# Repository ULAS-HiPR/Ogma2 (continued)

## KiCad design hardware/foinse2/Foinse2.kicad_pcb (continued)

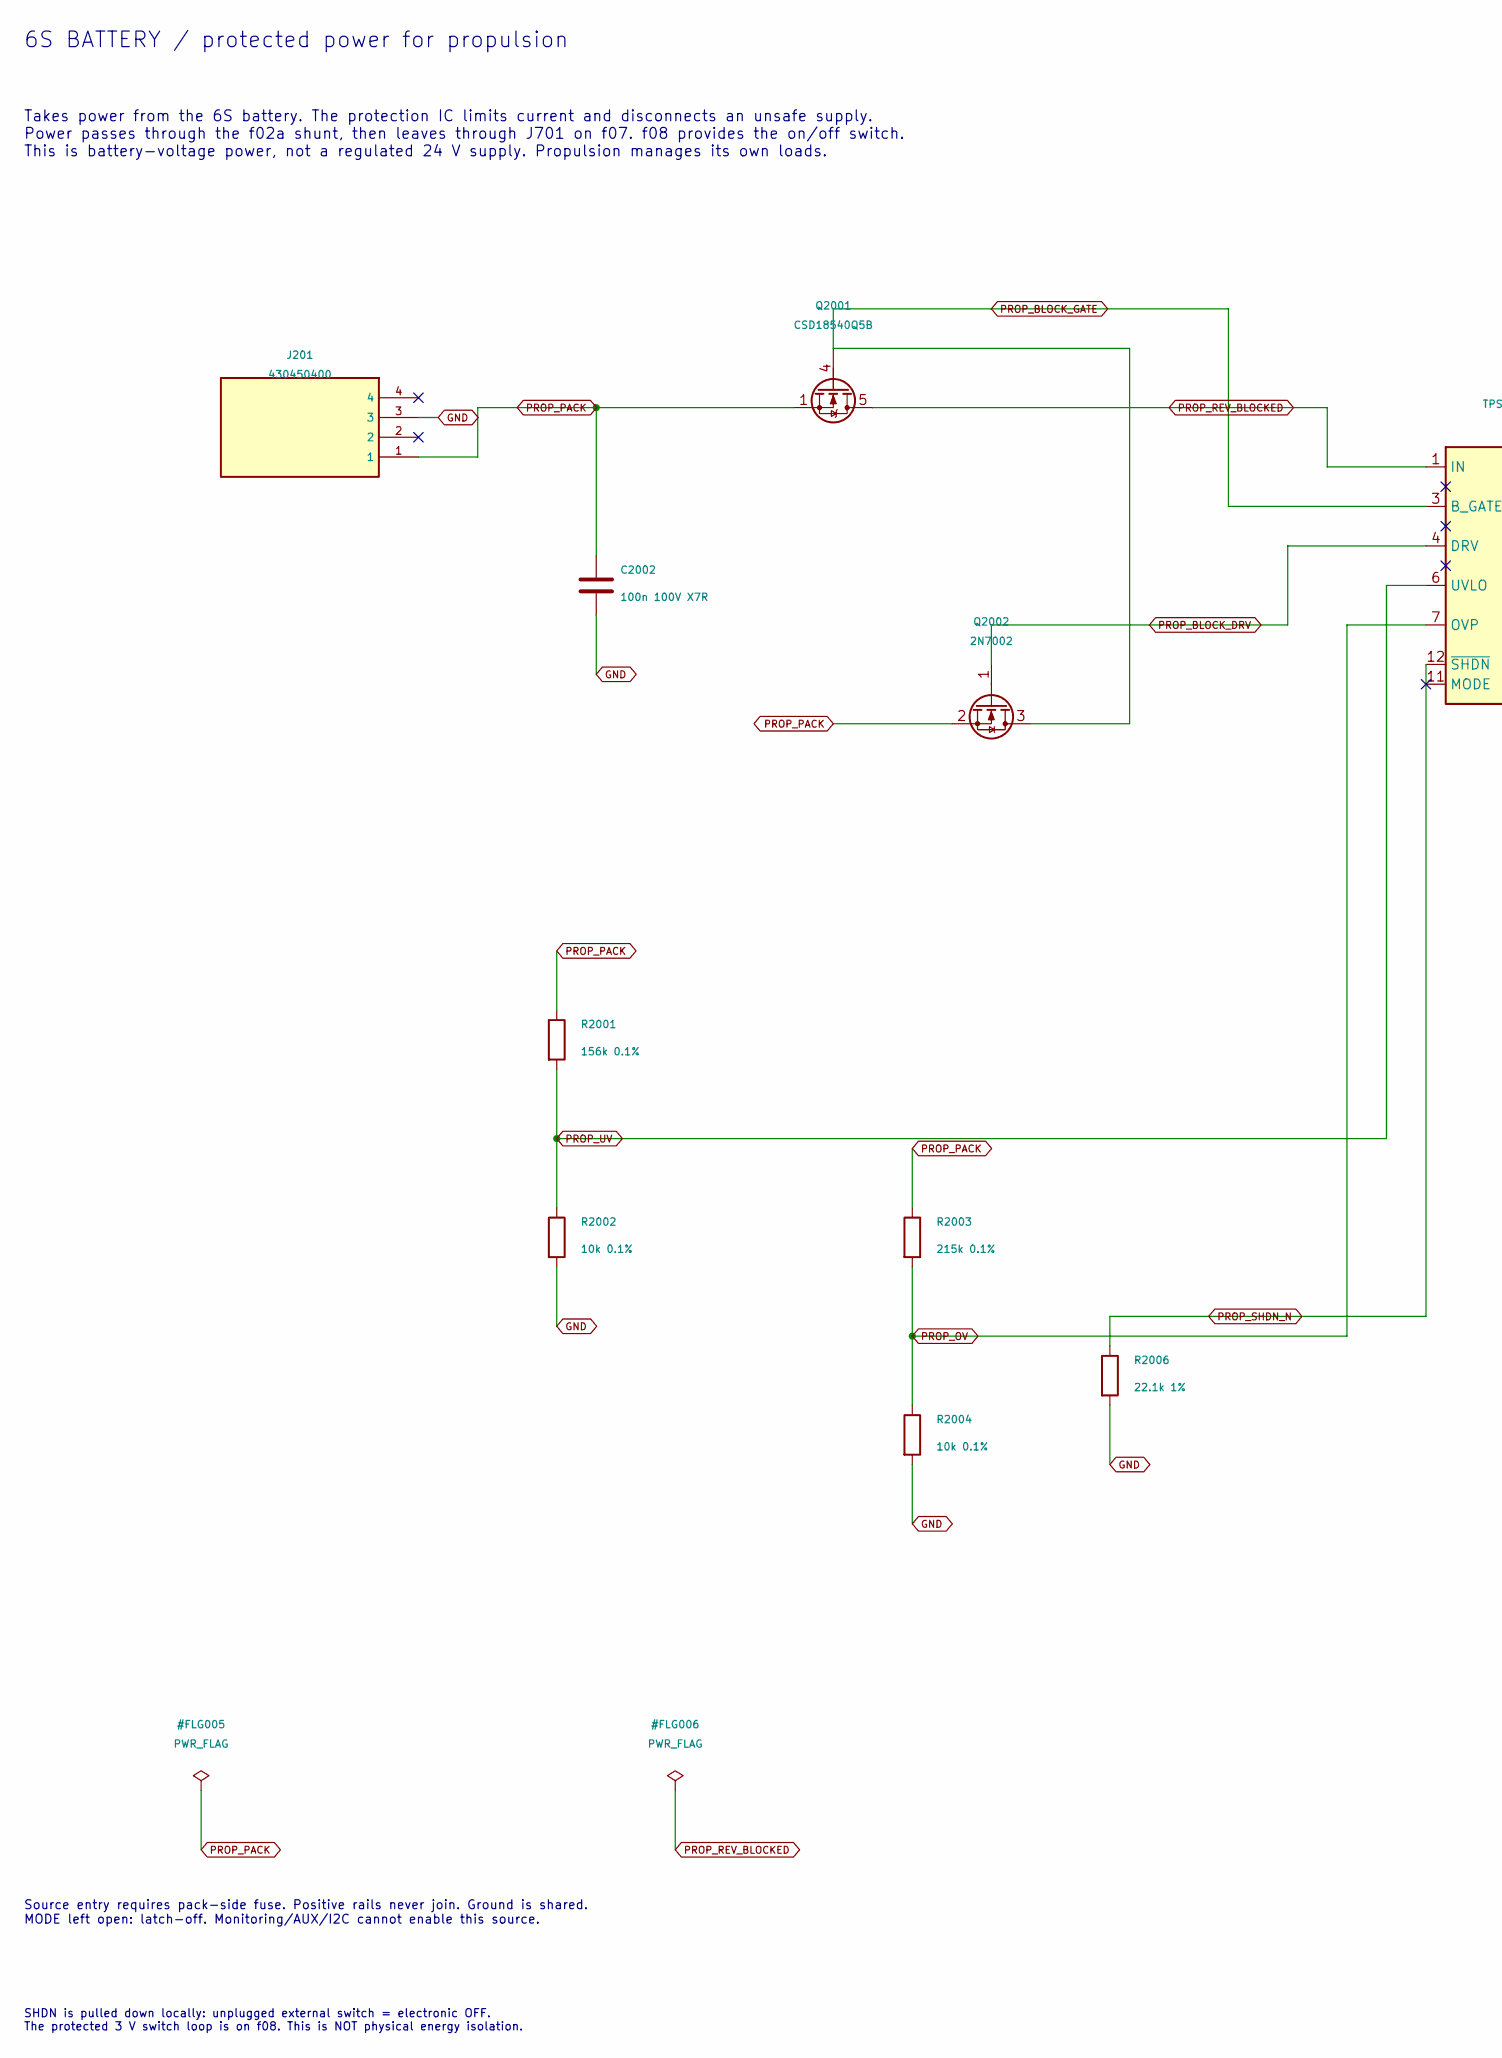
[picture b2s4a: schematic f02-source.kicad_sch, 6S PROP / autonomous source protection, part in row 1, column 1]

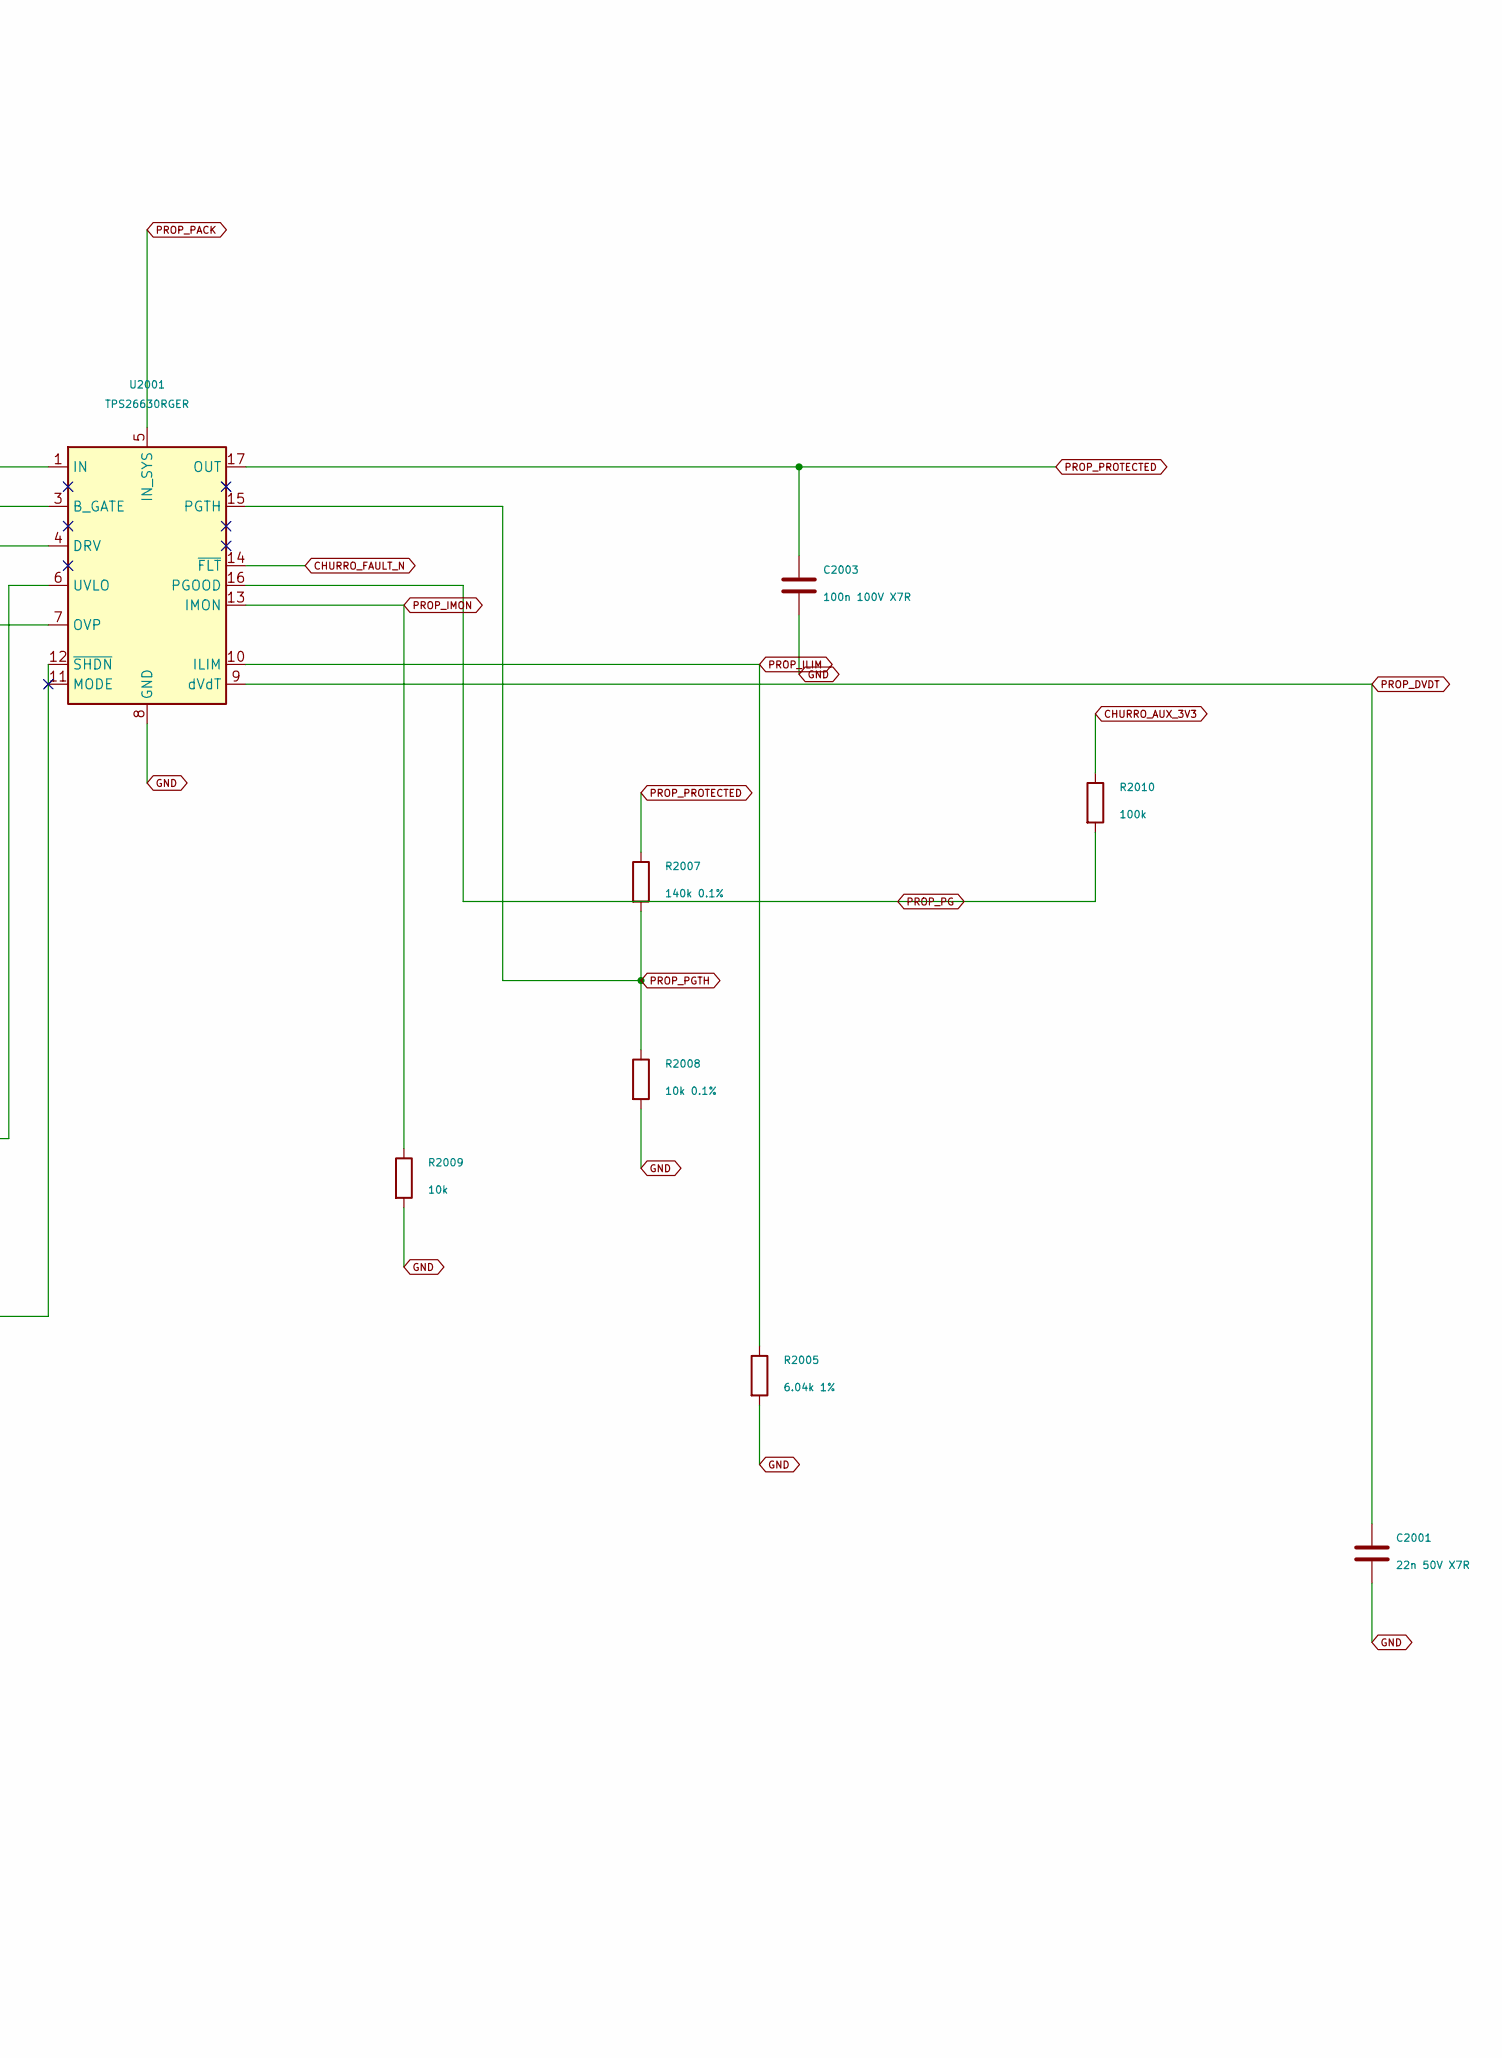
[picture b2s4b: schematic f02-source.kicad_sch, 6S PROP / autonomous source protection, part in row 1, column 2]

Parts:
C2001: 22n 50V X7R; C_0603_1608Metric
C2002, C2003: 100n 100V X7R; C_0603_1608Metric
J201: 430450400; MPN 430450400
Q2001: CSD18540Q5B; MPN CSD18540Q5B
Q2002: 2N7002; SOT-23
R2001: 156k 0.1%; R_0603_1608Metric
R2002, R2004, R2008: 10k 0.1%; R_0603_1608Metric
R2003: 215k 0.1%; R_0603_1608Metric
R2005: 6.04k 1%; R_0603_1608Metric
R2006: 22.1k 1%; R_0603_1608Metric
R2007: 140k 0.1%; R_0603_1608Metric
R2009: 10k; R_0603_1608Metric
R2010: 100k; R_0603_1608Metric
U2001: TPS26630RGER; MPN TPS26630RGER

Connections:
CHURRO_AUX_3V3: R2010.1; also elsewhere on the board
CHURRO_FAULT_N: U2001.14 (~FLT); also elsewhere on the board
GND: C2001.2, C2002.2, C2003.2, J201.3, R2002.2, R2004.2, R2005.2, R2006.2, R2008.2, R2009.2, U2001.8 (GND), U2001.25 (GND); also elsewhere on the board
PROP_BLOCK_DRV: Q2002.1 (G), U2001.4 (DRV)
PROP_BLOCK_GATE: Q2001.4 (G), Q2002.3 (D), U2001.3 (B_GATE); also elsewhere on the board
PROP_DVDT: C2001.1, U2001.9 (dVdT)
PROP_ILIM: R2005.1, U2001.10 (ILIM)
PROP_IMON: R2009.1, U2001.13 (IMON); also elsewhere on the board
PROP_OV: R2003.2, R2004.1, U2001.7 (OVP)
PROP_PACK: C2002.1, J201.1, Q2001.1 (S), Q2001.2 (S), Q2001.3 (S), Q2002.2 (S), R2001.1, R2003.1, U2001.5 (IN_SYS); also elsewhere on the board
PROP_PG: R2010.2, U2001.16 (PGOOD); also elsewhere on the board
PROP_PGTH: R2007.2, R2008.1, U2001.15 (PGTH)
PROP_PROTECTED: C2003.1, R2007.1, U2001.17 (OUT), U2001.18 (OUT); also elsewhere on the board
PROP_REV_BLOCKED: Q2001.5 (D), U2001.1 (IN), U2001.2 (IN); also elsewhere on the board
PROP_SHDN_N: R2006.1, U2001.12 (~SHDN); also elsewhere on the board
PROP_UV: R2001.2, R2002.1, U2001.6 (UVLO)

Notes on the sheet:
6S BATTERY / protected power for propulsion
Source entry requires pack-side fuse. Positive rails never join. Ground is shared. MODE left open: latch-off. Monitoring/AUX/I2C cannot enable this source.
SHDN is pulled down locally: unplugged external switch = electronic OFF. The protected 3 V switch loop is on f08. This is NOT physical energy isolation.
Takes power from the 6S battery. The protection IC limits current and disconnects an unsafe supply. Power passes through the f02a shunt, then leaves through J701 on f07. f08 provides the on/off switch. This is battery-voltage power, not a regulated 24 V supply. Propulsion manages its own loads.

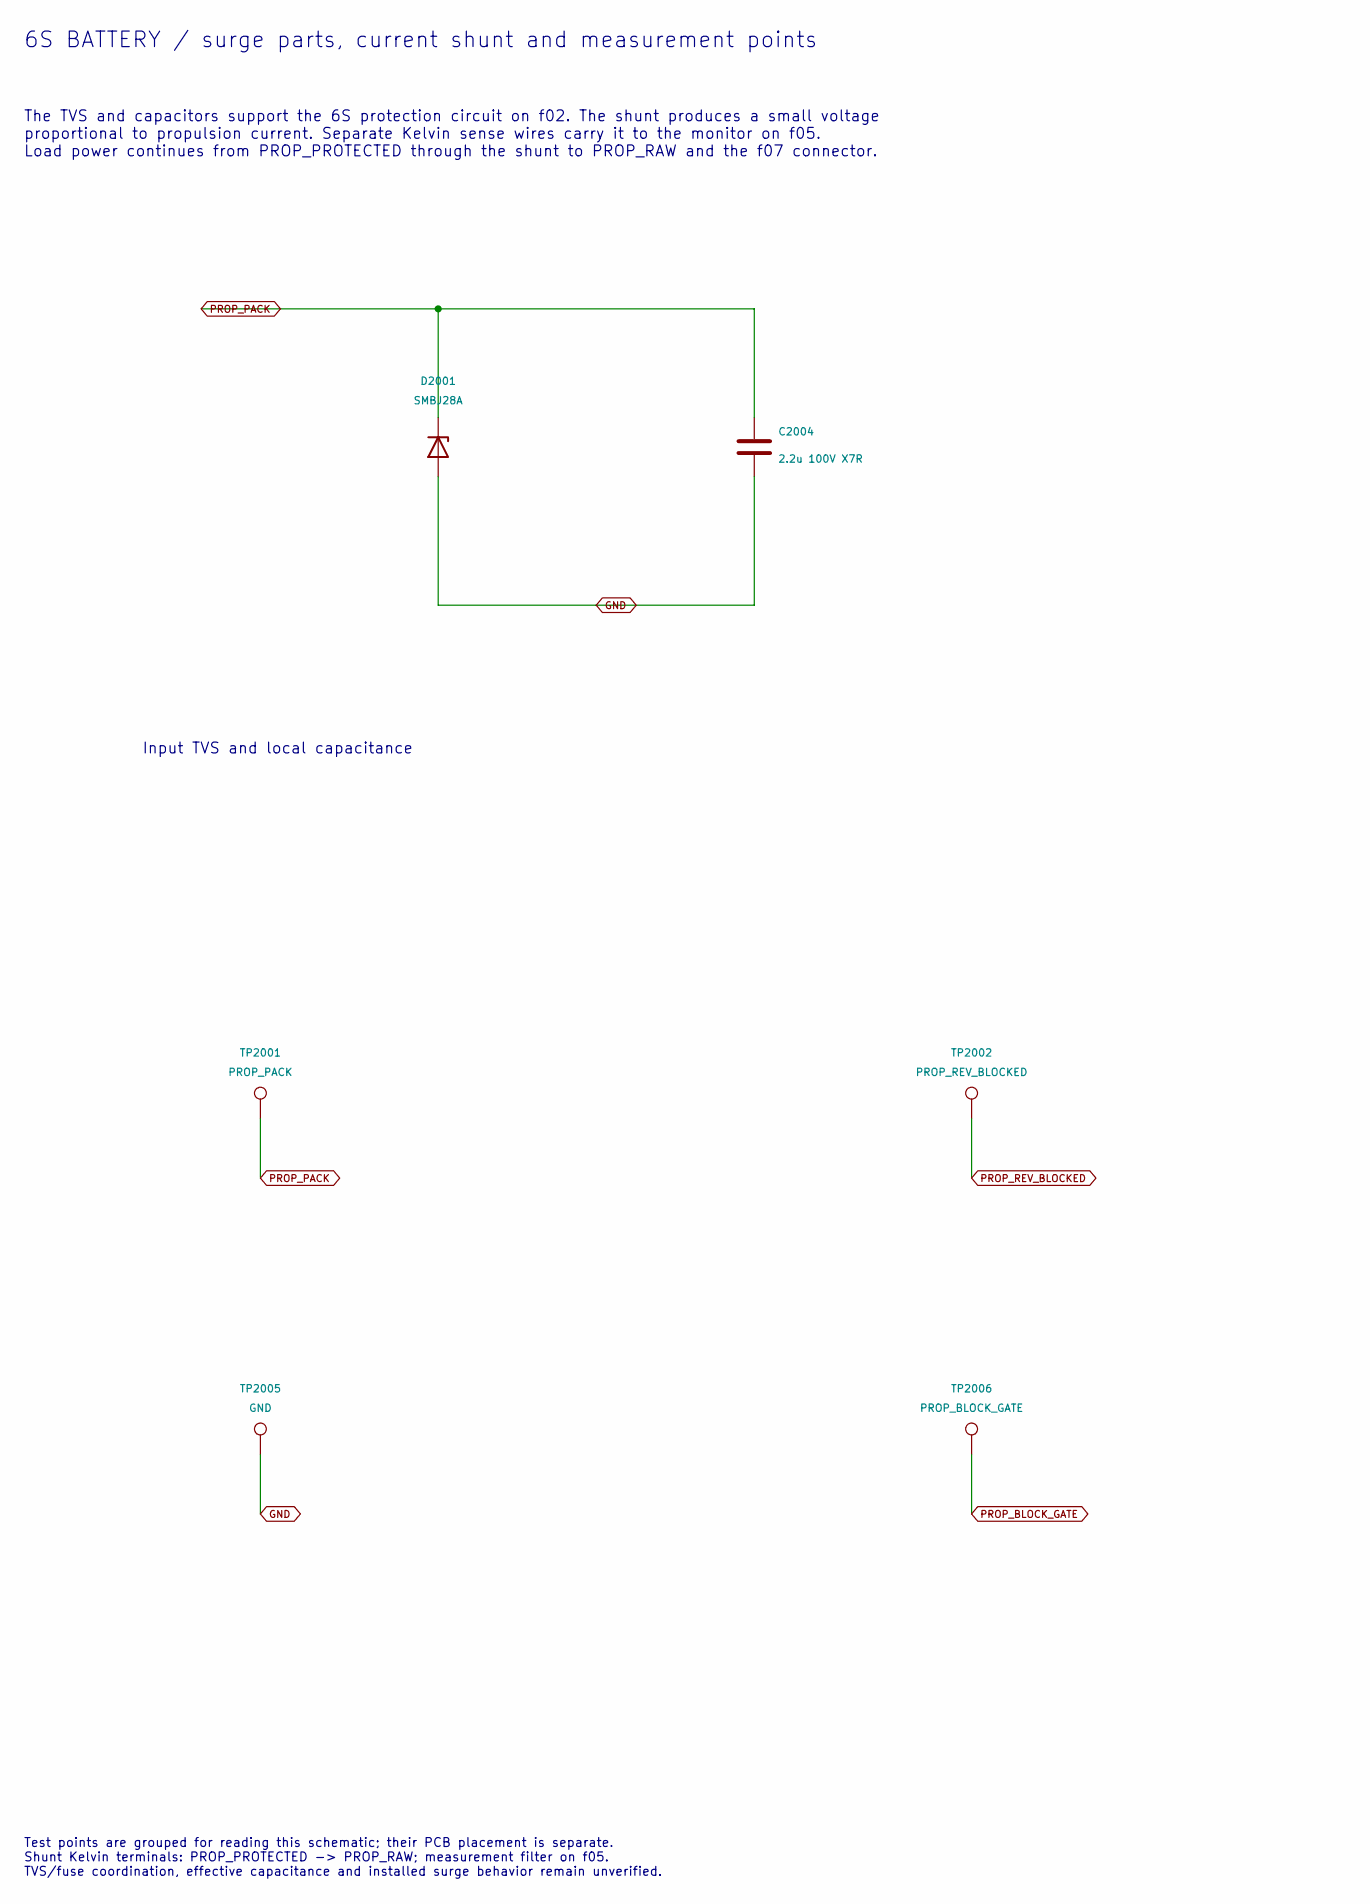
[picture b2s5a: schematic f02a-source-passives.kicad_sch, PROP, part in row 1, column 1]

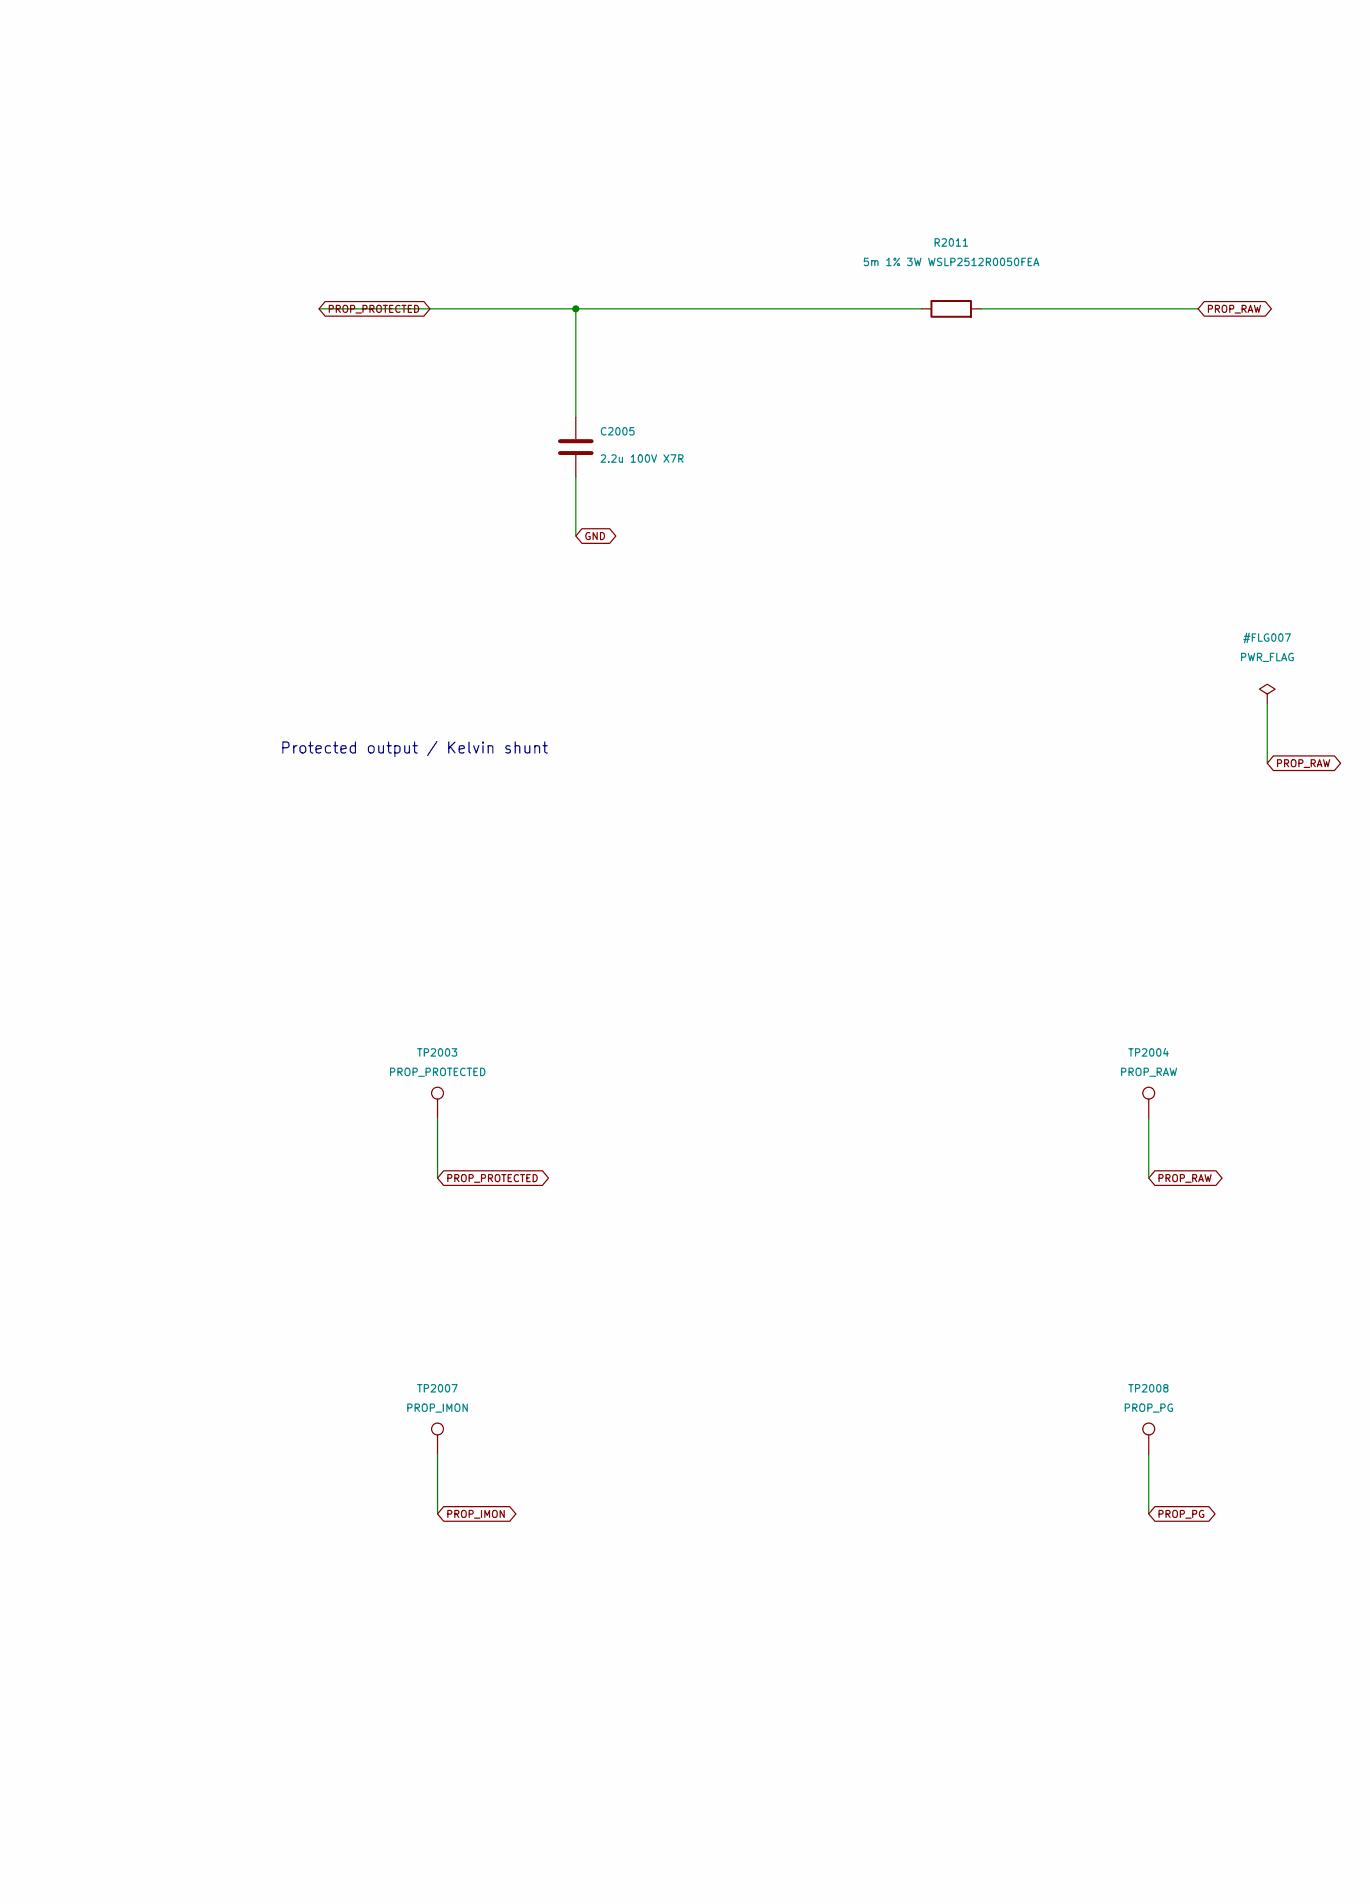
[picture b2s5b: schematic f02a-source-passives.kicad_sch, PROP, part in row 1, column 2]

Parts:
C2004, C2005: 2.2u 100V X7R; C_1210_3225Metric
D2001: SMBJ28A; D_SMB
R2011: 5m 1% 3W WSLP2512R0050FEA; R_2512_6332Metric
TP2001: PROP_PACK; TestPoint_Loop_D2.50mm_Drill1.0mm
TP2002: PROP_REV_BLOCKED; TestPoint_Loop_D2.50mm_Drill1.0mm
TP2003: PROP_PROTECTED; TestPoint_Loop_D2.50mm_Drill1.0mm
TP2004: PROP_RAW; TestPoint_Loop_D2.50mm_Drill1.0mm
TP2005: GND; TestPoint_Loop_D2.50mm_Drill1.0mm
TP2006: PROP_BLOCK_GATE; TestPoint_Pad_D1.0mm
TP2007: PROP_IMON; TestPoint_Pad_D1.0mm
TP2008: PROP_PG; TestPoint_Pad_D1.0mm

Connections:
GND: C2004.2, C2005.2, D2001.2 (A), TP2005.1; also elsewhere on the board
PROP_BLOCK_GATE: TP2006.1; also elsewhere on the board
PROP_IMON: TP2007.1; also elsewhere on the board
PROP_PACK: C2004.1, D2001.1 (K), TP2001.1; also elsewhere on the board
PROP_PG: TP2008.1; also elsewhere on the board
PROP_PROTECTED: C2005.1, R2011.1, TP2003.1; also elsewhere on the board
PROP_RAW: R2011.2, TP2004.1; also elsewhere on the board
PROP_REV_BLOCKED: TP2002.1; also elsewhere on the board

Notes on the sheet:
6S BATTERY / surge parts, current shunt and measurement points
Input TVS and local capacitance
Protected output / Kelvin shunt
Test points are grouped for reading this schematic; their PCB placement is separate. Shunt Kelvin terminals: PROP_PROTECTED -> PROP_RAW; measurement filter on f05. TVS/fuse coordination, effective capacitance and installed surge behavior remain unverified.
The TVS and capacitors support the 6S protection circuit on f02. The shunt produces a small voltage proportional to propulsion current. Separate Kelvin sense wires carry it to the monitor on f05. Load power continues from PROP_PROTECTED through the shunt to PROP_RAW and the f07 connector.

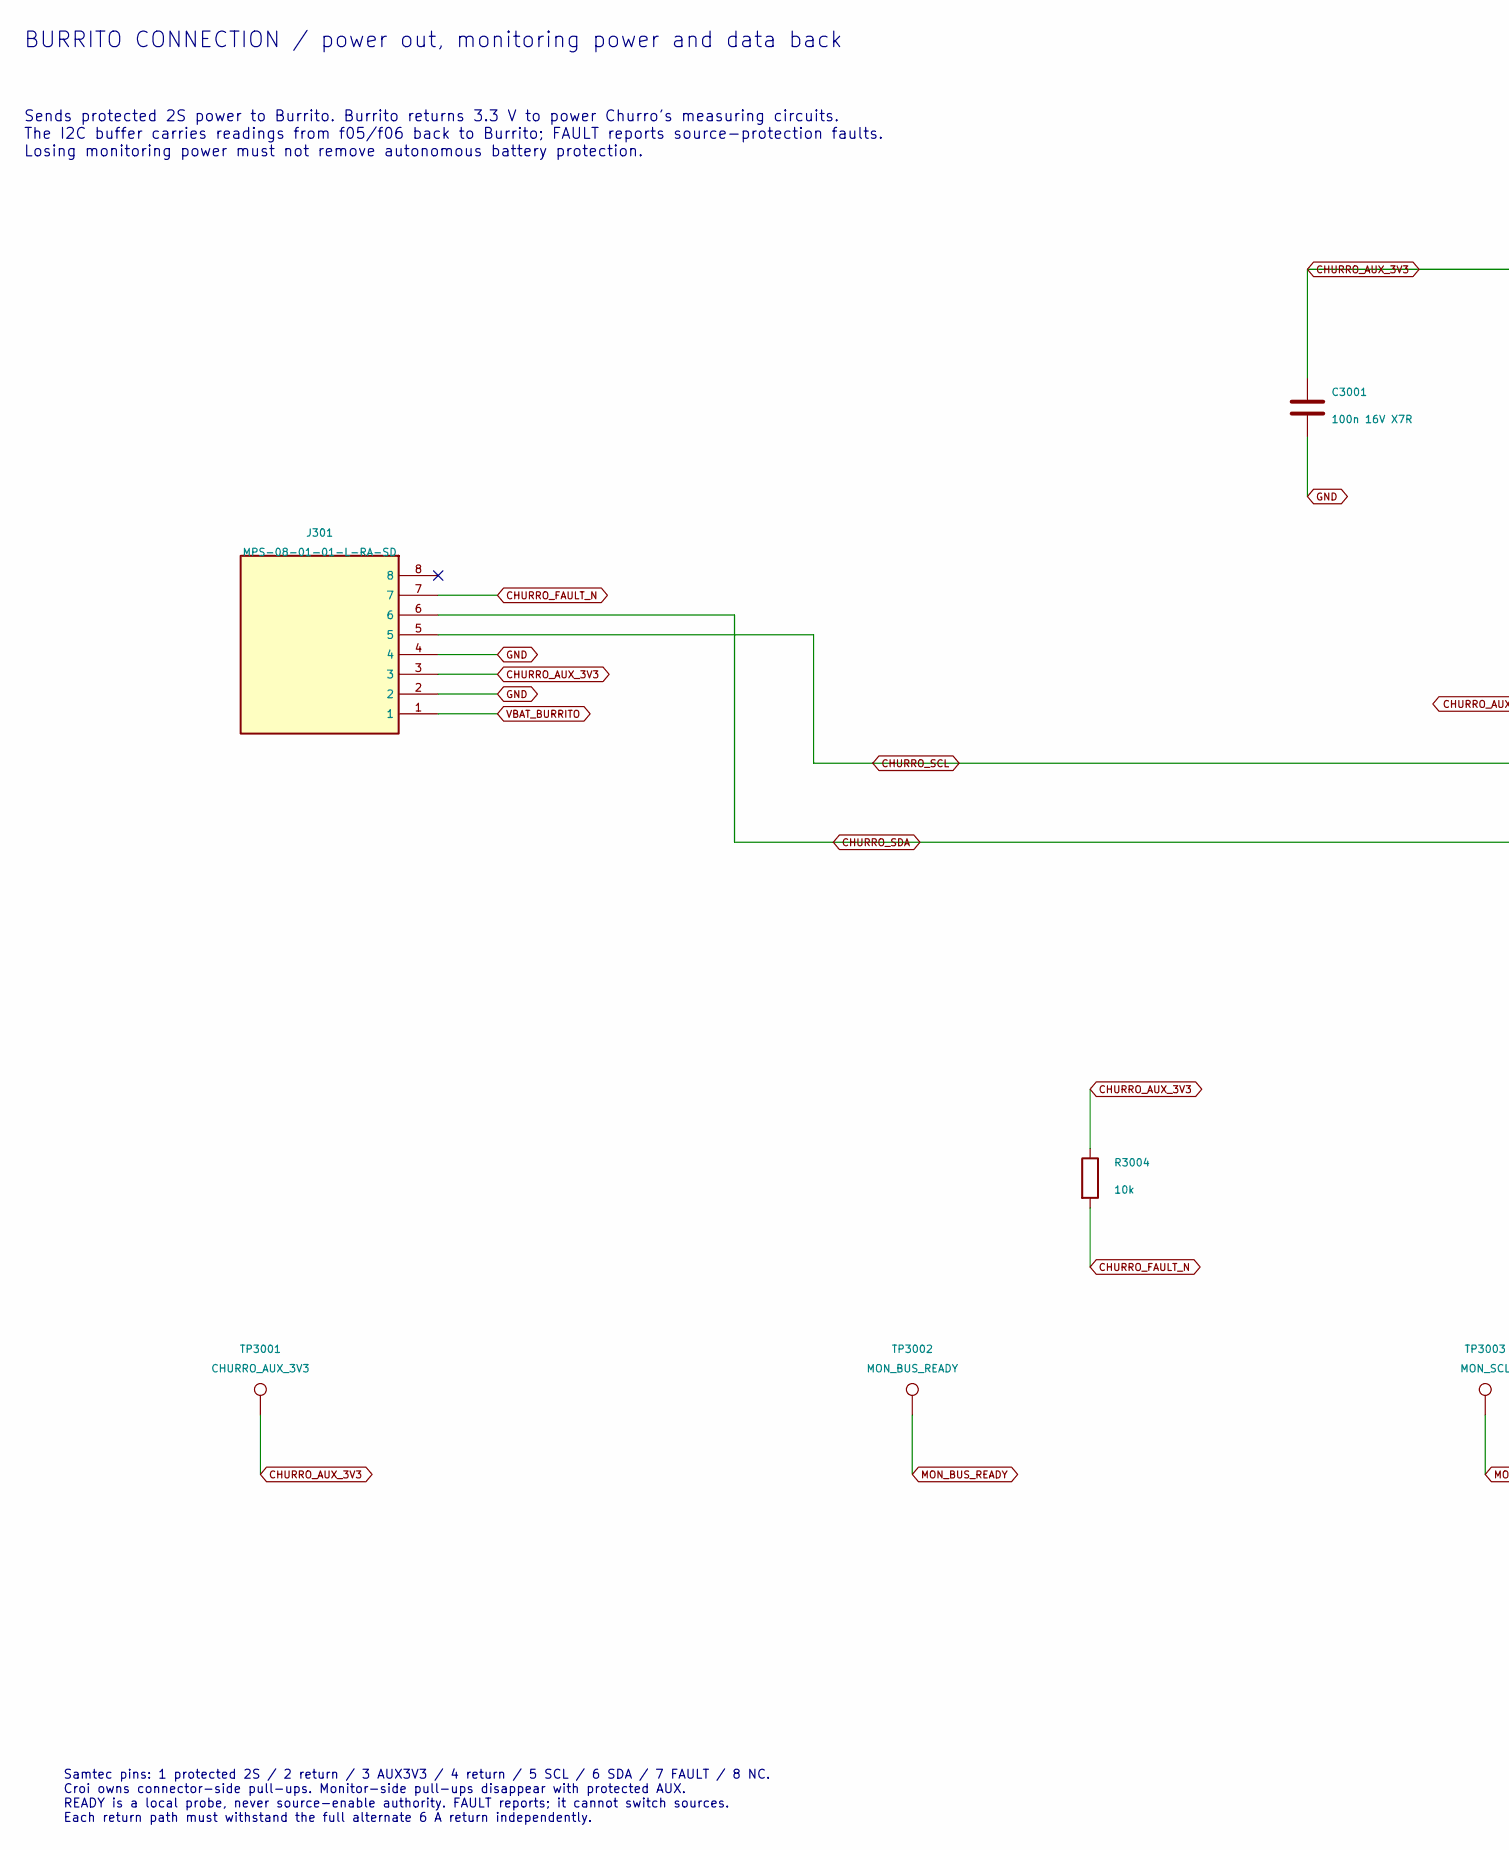
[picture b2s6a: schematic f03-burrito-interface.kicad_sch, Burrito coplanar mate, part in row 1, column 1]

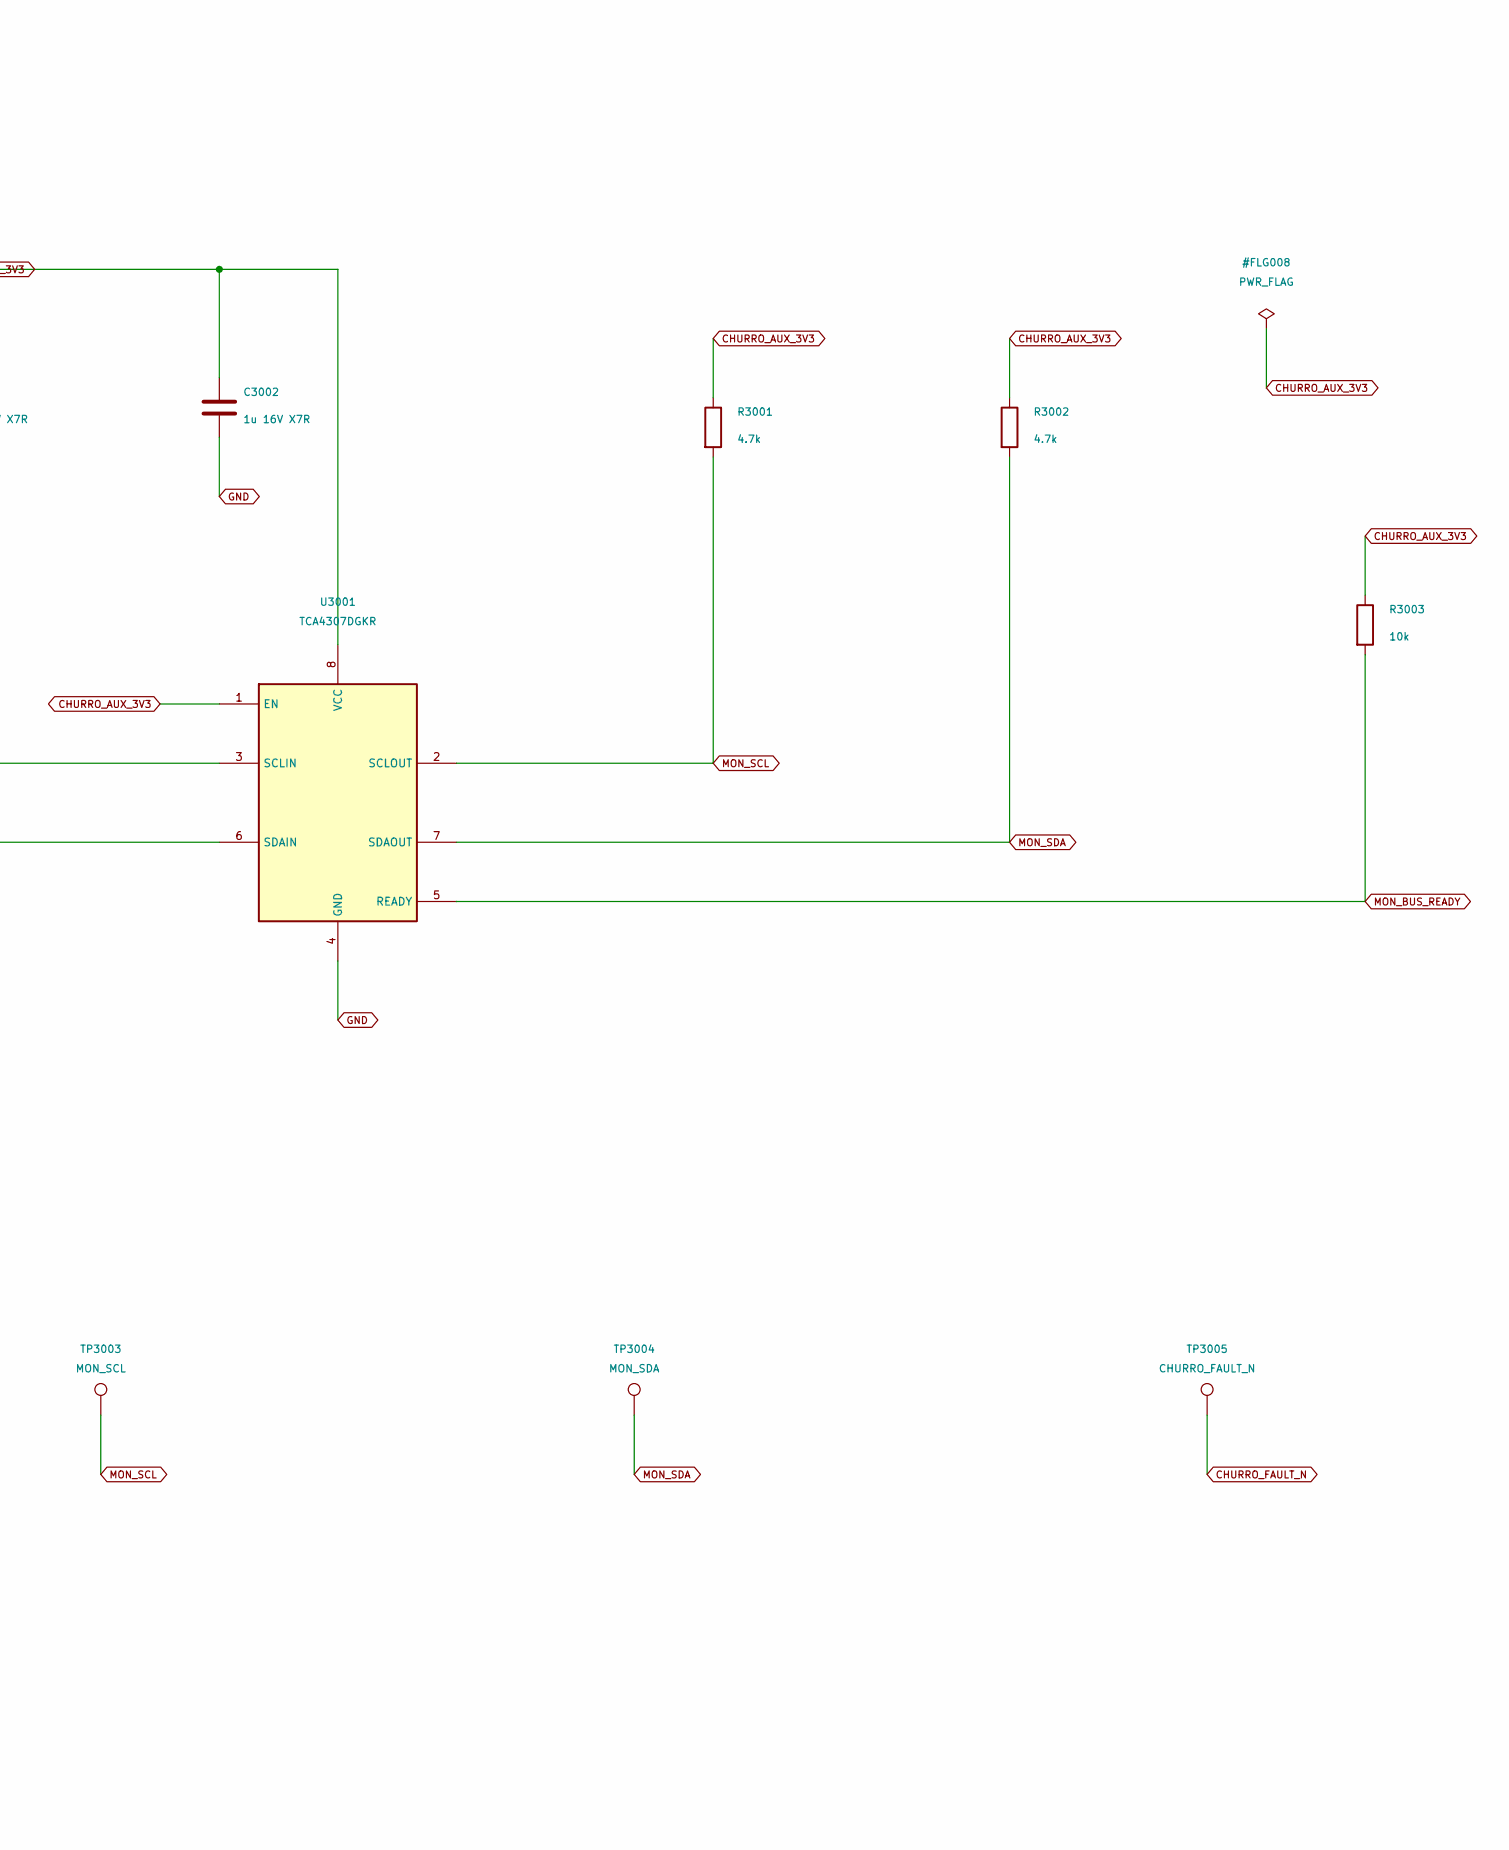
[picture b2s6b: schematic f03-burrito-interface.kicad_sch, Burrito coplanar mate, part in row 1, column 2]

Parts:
C3001: 100n 16V X7R; C_0603_1608Metric
C3002: 1u 16V X7R; C_0603_1608Metric
J301: MPS-08-01-01-L-RA-SD; MPN MPS-08-01-01-L-RA-SD
R3001, R3002: 4.7k; R_0603_1608Metric
R3003, R3004: 10k; R_0603_1608Metric
TP3001: CHURRO_AUX_3V3; TestPoint_Loop_D2.50mm_Drill1.0mm
TP3002: MON_BUS_READY; TestPoint_Pad_D1.0mm
TP3003: MON_SCL; TestPoint_Pad_D1.0mm
TP3004: MON_SDA; TestPoint_Pad_D1.0mm
TP3005: CHURRO_FAULT_N; TestPoint_Pad_D1.0mm
U3001: TCA4307DGKR; MPN TCA4307DGKR

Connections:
CHURRO_AUX_3V3: C3001.1, C3002.1, J301.3, R3001.1, R3002.1, R3003.1, R3004.1, TP3001.1, U3001.1 (EN), U3001.8 (VCC); also elsewhere on the board
CHURRO_FAULT_N: J301.7, R3004.2, TP3005.1; also elsewhere on the board
CHURRO_SCL: J301.5, U3001.3 (SCLIN)
CHURRO_SDA: J301.6, U3001.6 (SDAIN)
GND: C3001.2, C3002.2, J301.2, J301.4, U3001.4 (GND); also elsewhere on the board
MON_BUS_READY: R3003.2, TP3002.1, U3001.5 (READY)
MON_SCL: R3001.2, TP3003.1, U3001.2 (SCLOUT); also elsewhere on the board
MON_SDA: R3002.2, TP3004.1, U3001.7 (SDAOUT); also elsewhere on the board
VBAT_BURRITO: J301.1; also elsewhere on the board

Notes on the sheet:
BURRITO CONNECTION / power out, monitoring power and data back
Samtec pins: 1 protected 2S / 2 return / 3 AUX3V3 / 4 return / 5 SCL / 6 SDA / 7 FAULT / 8 NC. Croi owns connector-side pull-ups. Monitor-side pull-ups disappear with protected AUX. READY is a local probe, never source-enable authority. FAULT reports; it cannot switch sources. Each return path must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
Sends protected 2S power to Burrito. Burrito returns 3.3 V to power Churro's measuring circuits. The I2C buffer carries readings from f05/f06 back to Burrito; FAULT reports source-protection faults. Losing monitoring power must not remove autonomous battery protection.

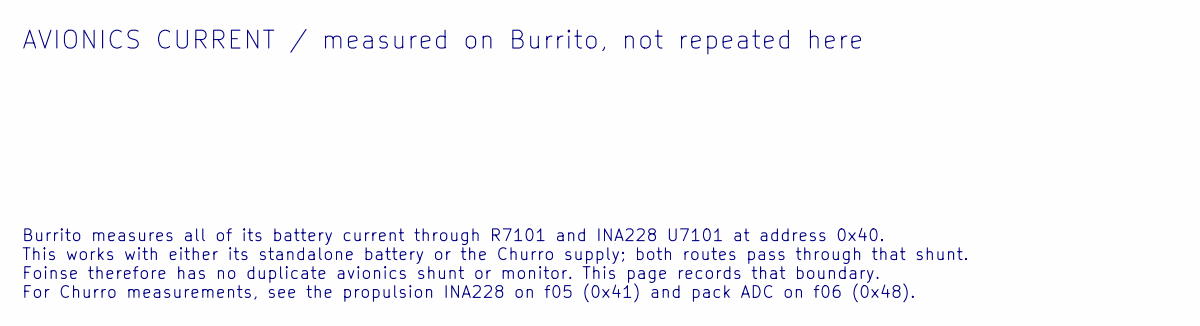
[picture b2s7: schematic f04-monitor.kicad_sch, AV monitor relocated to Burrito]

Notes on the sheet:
AVIONICS CURRENT / measured on Burrito, not repeated here
Burrito measures all of its battery current through R7101 and INA228 U7101 at address 0x40. This works with either its standalone battery or the Churro supply; both routes pass through that shunt. Foinse therefore has no duplicate avionics shunt or monitor. This page records that boundary. For Chur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
